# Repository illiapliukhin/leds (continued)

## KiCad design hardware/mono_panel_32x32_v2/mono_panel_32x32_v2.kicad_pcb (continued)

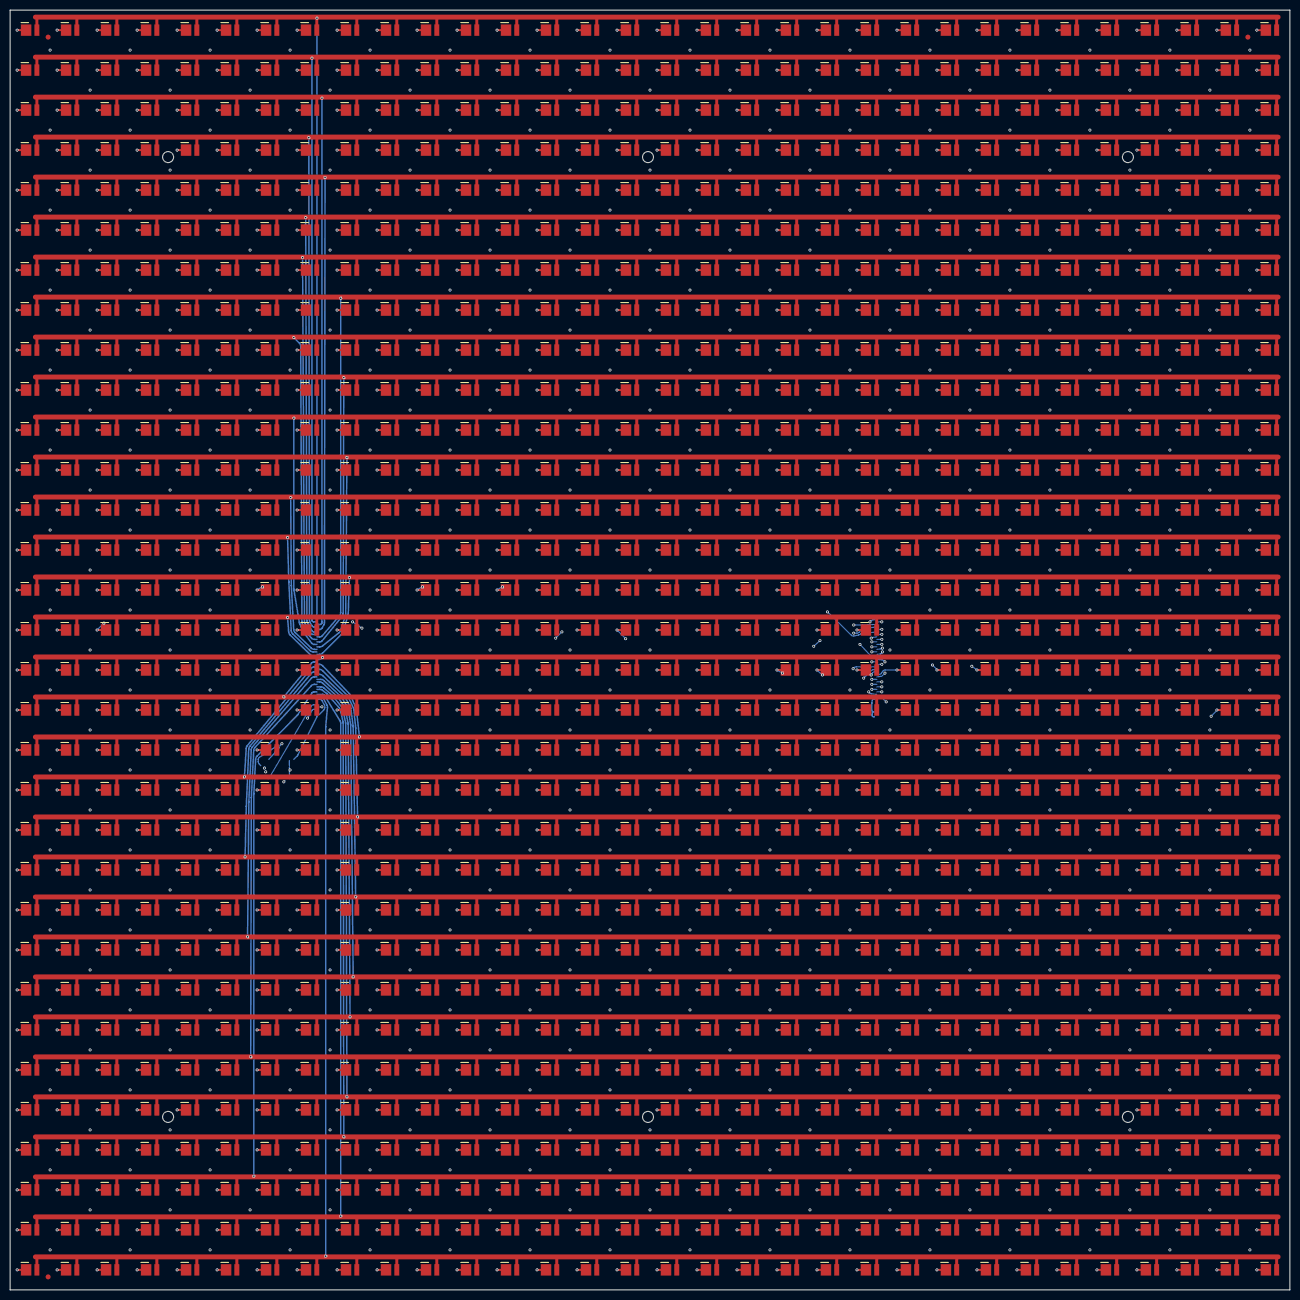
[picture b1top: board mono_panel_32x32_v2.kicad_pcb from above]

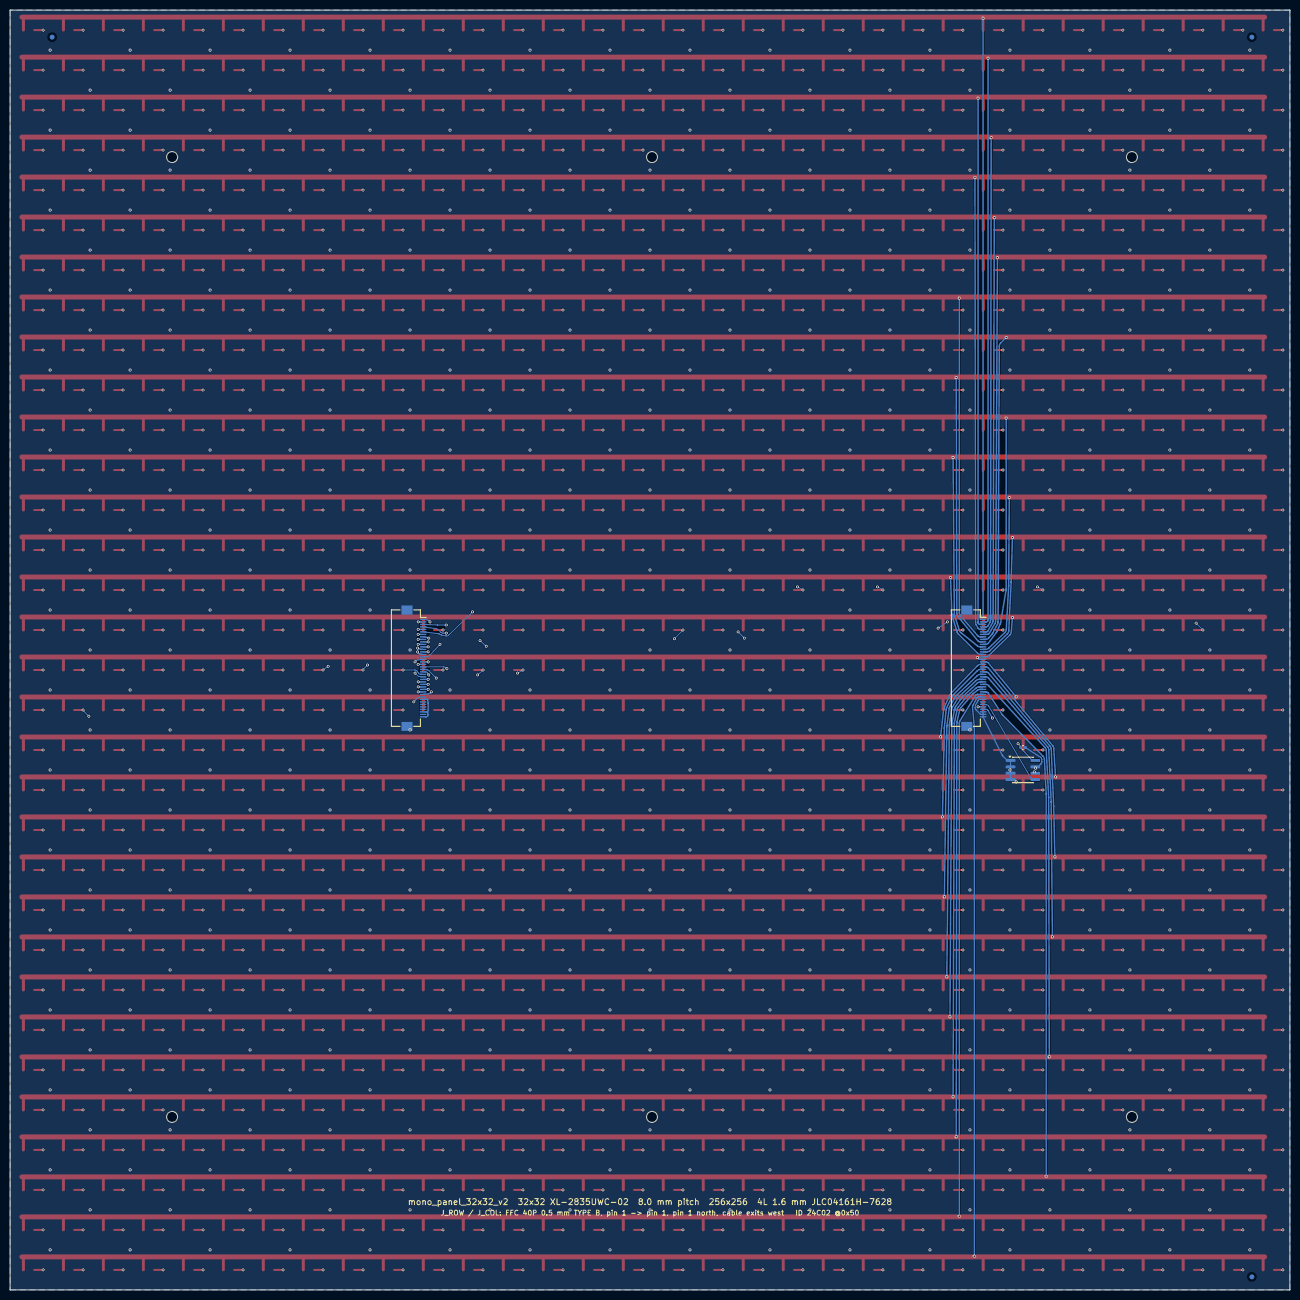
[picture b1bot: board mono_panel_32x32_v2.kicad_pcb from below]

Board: 4 copper layers, 256.0 x 256.0 mm, 1040 parts (7 on the bottom side), 68 nets.

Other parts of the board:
FID1, FID2, FID3, FID4, FID5, FID6: Fiducial; Fiducial_1mm_Mask2mm
MH1, MH2, MH3, MH4, MH5, MH6: MountingHole_M2; MountingHole_2.2mm_M2_NPTH_Cell

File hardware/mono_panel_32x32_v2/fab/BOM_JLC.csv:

Comment,Designator,Footprint,LCSC Part #,Qty
XINGLIGHT XL-2835UWC-02,"D1,D2,D3,D4,D5,D6,D7,D8,D9,D10,D11,D12,D13,D14,D15,D16,D17,D18,D19,D20,D21,D22,D23,D24,D25,D26,D27,D28,D29,D30,D31,D32,D33,D34,D35,D36,D37,D38,D39,D40,D41,D42,D43,D44,D45,D46,D47,D48,D49,D50,D51,D52,D53,D54,D55,D56,D57,D58,D59,D60,D61,D62,D63,D64,D65,D66,D67,D68,D69,D70,D71,D72,D73,D74,D75,D76,D77,D78,D79,D80,D81,D82,D83,D84,D85,D86,D87,D88,D89,D90,D91,D92,D93,D94,D95,D96,D97,D98,D99,D100,D101,D102,D103,D104,D105,D106,D107,D108,D109,D110,D111,D112,D113,D114,D115,D116,D117,D118,D119,D120,D121,D122,D123,D124,D125,D126,D127,D128,D129,D130,D131,D132,D133,D134,D135,D136,D137,D138,D139,D140,D141,D142,D143,D144,D145,D146,D147,D148,D149,D150,D151,D152,D153,D154,D155,D156,D157,D158,D159,D160,D161,D162,D163,D164,D165,D166,D167,D168,D169,D170,D171,D172,D173,D174,D175,D176,D177,D178,D179,D180,D181,D182,D183,D184,D185,D186,D187,D188,D189,D190,D191,D192,D193,D194,D195,D196,D197,D198,D199,D200,D201,D202,D203,D204,D205,D206,D207,D208,D209,D210,D211,D212,D213,D214,D215,D216,D217,D218,D219,D220,D221,D222,D223,D224,D225,D226,D227,D228,D229,D230,D231,D232,D233,D234,D235,D236,D237,D238,D239,D240,D241,D242,D243,D244,D245,D246,D247,D248,D249,D250,D251,D252,D253,D254,D255,D256,D257,D258,D259,D260,D261,D262,D263,D264,D265,D266,D267,D268,D269,D270,D271,D272,D273,D274,D275,D276,D277,D278,D279,D280,D281,D282,D283,D284,D285,D286,D287,D288,D289,D290,D291,D292,D293,D294,D295,D296,D297,D298,D299,D300,D301,D302,D303,D304,D305,D306,D307,D308,D309,D310,D311,D312,D313,D314,D315,D316,D317,D318,D319,D320,D321,D322,D323,D324,D325,D326,D327,D328,D329,D330,D331,D332,D333,D334,D335,D336,D337,D338,D339,D340,D341,D342,D343,D344,D345,D346,D347,D348,D349,D350,D351,D352,D353,D354,D355,D356,D357,D358,D359,D360,D361,D362,D363,D364,D365,D366,D367,D368,D369,D370,D371,D372,D373,D374,D375,D376,D377,D378,D379,D380,D381,D382,D383,D384,D385,D386,D387,D388,D389,D390,D391,D392,D393,D394,D395,D396,D397,D398,D399,D400,D401,D402,D403,D404,D405,D406,D407,D408,D409,D410,D411,D412,D413,D414,D415,D416,D417,D418,D419,D420,D421,D422,D423,D424,D425,D426,D427,D428,D429,D430,D431,D432,D433,D434,D435,D436,D437,D438,D439,D440,D441,D442,D443,D444,D445,D446,D447,D448,D449,D450,D451,D452,D453,D454,D455,D456,D457,D458,D459,D460,D461,D462,D463,D464,D465,D466,D467,D468,D469,D470,D471,D472,D473,D474,D475,D476,D477,D478,D479,D480,D481,D482,D483,D484,D485,D486,D487,D488,D489,D490,D491,D492,D493,D494,D495,D496,D497,D498,D499,D500,D501,D502,D503,D504,D505,D506,D507,D508,D509,D510,D511,D512,D513,D514,D515,D516,D517,D518,D519,D520,D521,D522,D523,D524,D525,D526,D527,D528,D529,D530,D531,D532,D533,D534,D535,D536,D537,D538,D539,D540,D541,D542,D543,D544,D545,D546,D547,D548,D549,D550,D551,D552,D553,D554,D555,D556,D557,D558,D559,D560,D561,D562,D563,D564,D565,D566,D567,D568,D569,D570,D571,D572,D573,D574,D575,D576,D577,D578,D579,D580,D581,D582,D583,D584,D585,D586,D587,D588,D589,D590,D591,D592,D593,D594,D595,D596,D597,D598,D599,D600,D601,D602,D603,D604,D605,D606,D607,D608,D609,D610,D611,D612,D613,D614,D615,D616,D617,D618,D619,D620,D621,D622,D623,D624,D625,D626,D627,D628,D629,D630,D631,D632,D633,D634,D635,D636,D637,D638,D639,D640,D641,D642,D643,D644,D645,D646,D647,D648,D649,D650,D651,D652,D653,D654,D655,D656,D657,D658,D659,D660,D661,D662,D663,D664,D665,D666,D667,D668,D669,D670,D671,D672,D673,D674,D675,D676,D677,D678,D679,D680,D681,D682,D683,D684,D685,D686,D687,D688,D689,D690,D691,D692,D693,D694,D695,D696,D697,D698,D699,D700,D701,D702,D703,D704,D705,D706,D707,D708,D709,D710,D711,D712,D713,D714,D715,D716,D717,D718,D719,D720,D721,D722,D723,D724,D725,D726,D727,D728,D729,D730,D731,D732,D733,D734,D735,D736,D737,D738,D739,D740,D741,D742,D743,D744,D745,D746,D747,D748,D749,D750,D751,D752,D753,D754,D755,D756,D757,D758,D759,D760,D761,D762,D763,D764,D765,D766,D767,D768,D769,D770,D771,D772,D773,D774,D775,D776,D777,D778,D779,D780,D781,D782,D783,D784,D785,D786,D787,D788,D789,D790,D791,D792,D793,D794,D795,D796,D797,D798,D799,D800,D801,D802,D803,D804,D805,D806,D807,D808,D809,D810,D811,D812,D813,D814,D815,D816,D817,D818,D819,D820,D821,D822,D823,D824,D825,D826,D827,D828,D829,D830,D831,D832,D833,D834,D835,D836,D837,D838,D839,D840,D841,D842,D843,D844,D845,D846,D847,D848,D849,D850,D851,D852,D853,D854,D855,D856,D857,D858,D859,D860,D861,D862,D863,D864,D865,D866,D867,D868,D869,D870,D871,D872,D873,D874,D875,D876,D877,D878,D879,D880,D881,D882,D883,D884,D885,D886,D887,D888,D889,D890,D891,D892,D893,D894,D895,D896,D897,D898,D899,D900,D901,D902,D903,D904,D905,D906,D907,D908,D909,D910,D911,D912,D913,D914,D915,D916,D917,D918,D919,D920,D921,D922,D923,D924,D925,D926,D927,D928,D929,D930,D931,D932,D933,D934,D935,D936,D937,D938,D939,D940,D941,D942,D943,D944,D945,D946,D947,D948,D949,D950,D951,D952,D953,D954,D955,D956,D957,D958,D959,D960,D961,D962,D963,D964,D965,D966,D967,D968,D969,D970,D971,D972,D973,D974,D975,D976,D977,D978,D979,D980,D981,D982,D983,D984,D985,D986,D987,D988,D989,D990,D991,D992,D993,D994,D995,D996,D997,D998,D999,D1000,D1001,D1002,D1003,D1004,D1005,D1006,D1007,D1008,D1009,D1010,D1011,D1012,D1013,D1014,D1015,D1016,D1017,D1018,D1019,D1020,D1021,D1022,D1023,D1024",LED_2835_XL-2835UWC,C2843876,1024
Hirose FH12-40S-0.5SH(55),"J_ROW1,J_COL1",Hirose_FH12-40S-0.5SH_B,C202114,2
ST M24C02-WMN6TP,U_ID1,SOIC-8_3.9x4.9mm_P1.27mm,C7562,1
Samsung CL05B104KO5NNNC,C_ID1,C_0402_1005Metric,C1525,1
